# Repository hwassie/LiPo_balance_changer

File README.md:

# LiPo_balance_changer
LiPo_balance_changer

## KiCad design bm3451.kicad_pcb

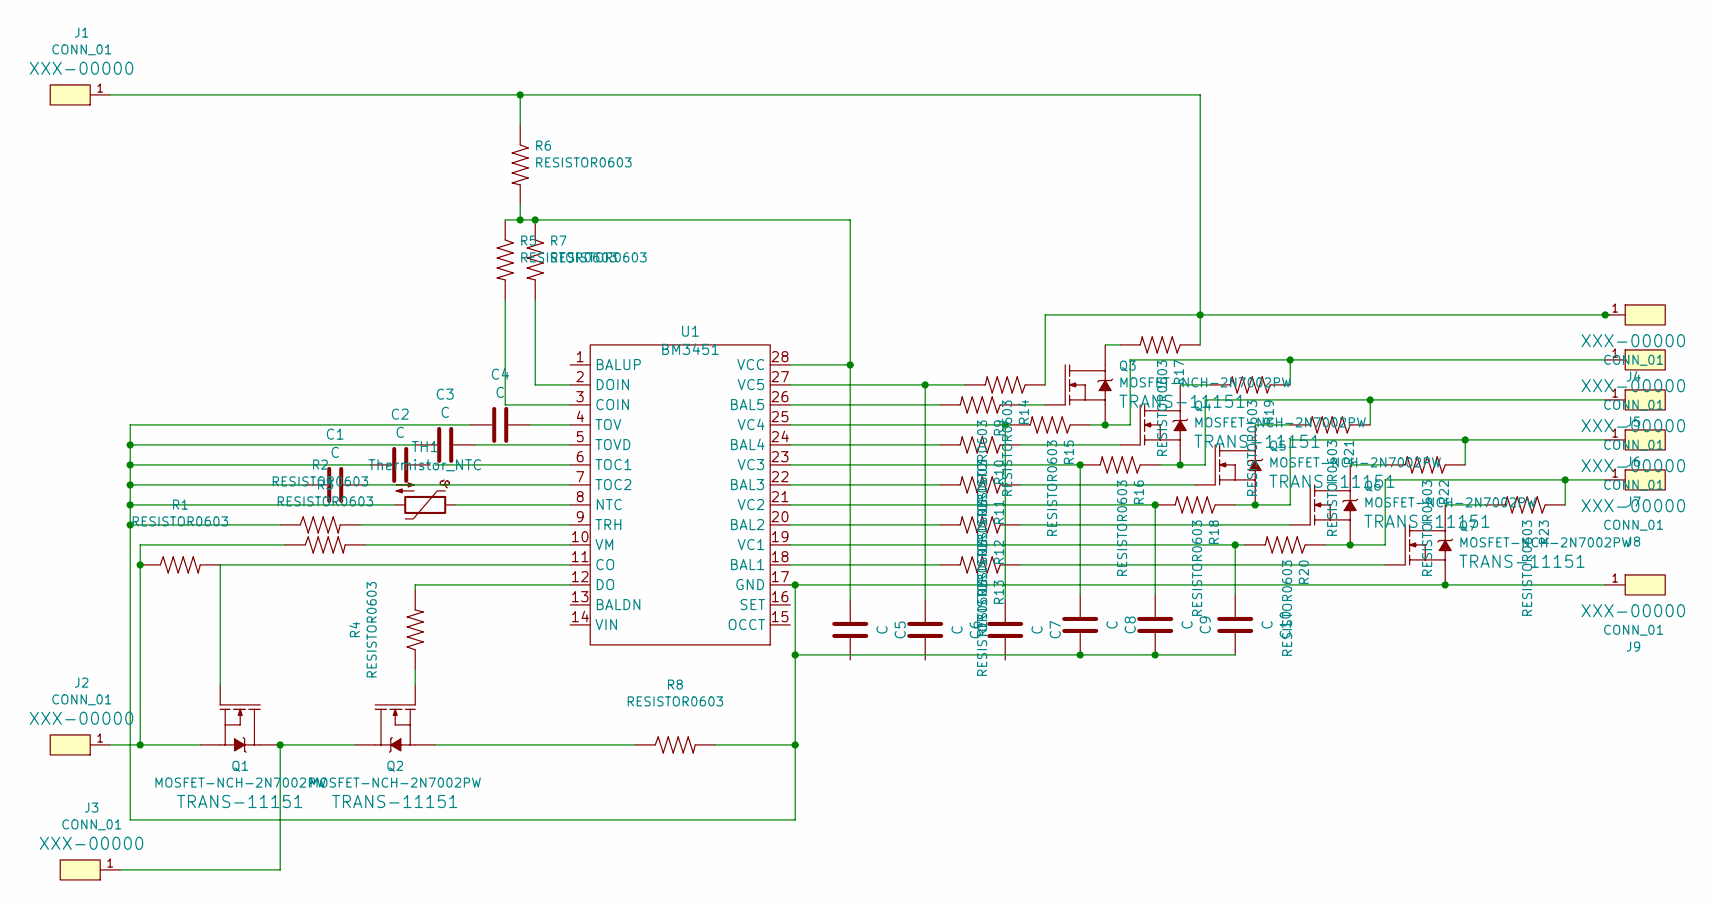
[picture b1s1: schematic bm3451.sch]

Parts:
C1, C2, C3, C4, C5, C6, C7, C8, C9, C10: C; 0603
J1, J2, J3, J4, J5, J6, J7, J8, J9: CONN_01; 1X01
Q1, Q2: MOSFET-NCH-2N7002PW; TO-252-2
Q3, Q4, Q5, Q6, Q7: MOSFET-NCH-2N7002PW; SOT-23
R1, R2, R3, R4, R5, R6, R7, R8, R9, R10, R11, R12, R13, R14, R15, R16, R17, R18, R19, R20, R21, R22, R23: RESISTOR0603; 0603
TH1: Thermistor_NTC; LED-0603
U1: BM3451; TSSOP-28_4.4x9.7mm_P0.65mm

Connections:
unnamed: C1.1, U1.7 (TOC2)
unnamed: C1.2, C2.2, C3.2, C4.2, C8.1, C9.1, C10.1, J9.1, Q7.2 (S), R2.1, R8.2, TH1.2, U1.17 (GND)
unnamed: C3.1, U1.5 (TOVD)
unnamed: C4.1, U1.4 (TOV)
unnamed: C5.2, R5.1, R6.2, R7.1, U1.28 (VCC)
unnamed: C6.2, R14.2, U1.27 (VC5)
unnamed: C7.2, R15.2, U1.25 (VC4)
unnamed: C8.2, R16.2, U1.23 (VC3)
unnamed: C9.2, R18.2, U1.21 (VC2)
unnamed: C10.2, R20.2, U1.19 (VC1)
unnamed: J1.1, J4.1, R6.1, R14.1, R17.1
unnamed: J2.1, Q1.2 (S), R1.1, R3.1
unnamed: J3.1, Q1.3 (D), Q2.3 (D)
unnamed: J5.1, Q3.2 (S), R15.1, R19.1
unnamed: J6.1, Q4.2 (S), R16.1, R21.1
unnamed: J7.1, Q5.2 (S), R18.1, R22.1
unnamed: J8.1, Q6.2 (S), R20.1, R23.1
unnamed: Q1.1 (G), R1.2, U1.11 (CO)
unnamed: Q2.1 (G), R4.1
unnamed: Q2.2 (S), R8.1
unnamed: Q3.1 (G), R9.1
unnamed: Q3.3 (D), R17.2
unnamed: Q4.1 (G), R10.1
unnamed: Q4.3 (D), R19.2
unnamed: Q5.1 (G), R11.1
unnamed: Q5.3 (D), R21.2
unnamed: Q6.1 (G), R12.1
unnamed: Q6.3 (D), R22.2
unnamed: Q7.1 (G), R13.1
unnamed: Q7.3 (D), R23.2
unnamed: R2.2, U1.9 (TRH)
unnamed: R3.2, U1.10 (VM)
unnamed: R4.2, U1.12 (DO)
unnamed: R5.2, U1.3 (COIN)
unnamed: R7.2, U1.2 (DOIN)
unnamed: R9.2, U1.26 (BAL5)
unnamed: R10.2, U1.24 (BAL4)
unnamed: R11.2, U1.22 (BAL3)
unnamed: R12.2, U1.20 (BAL2)
unnamed: R13.2, U1.18 (BAL1)
unnamed: TH1.1, U1.8 (NTC)

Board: 2 copper layers, 51 parts (0 on the bottom side), 40 nets, no tracks yet.

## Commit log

2019-12-08 Add kicad files
